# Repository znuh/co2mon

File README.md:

# CO2 multimon

CO2 monitor with support for different sensors, displays and microcontrollers.

Firmware and the printed circuit board include support for all of these components.
No special boards or firmware versions are needed. Sensors and the display are automatically detected by the firmware.

## Supported CO2 sensors
* SCD30
* MH-Z14A, MH-Z19B
* T67xx

## Supported displays
* 1.8" SPI TFT (ST7735 controller)
* 1.3" OLED (**must** have the following pinout: Vdd, GND, SCK, SDA - most 0.96" OLED displays will not work!)
**Note:** Try to get the 1.8" TFT instead of the OLED. OLED displays will 'burn out' after approx. 1 month of continous use. Therefor OLED support is meant as a makeshift if you cannot get the TFT.

## Supported microcontrollers

### ATMega328P 'Nano V3' Boards
For this variant you need to solder a few 0805 resistors and 3x SOT-23 components to side B of the PCB.

### STM32F042K6T6 
Fot this variant you need to solder the LQFP-32 controller, a SOT-23 component, the micro-USB connector, a 1210 fuse and a few 0603 passives to side A of the PCB.

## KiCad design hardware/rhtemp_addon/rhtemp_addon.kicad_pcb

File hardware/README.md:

## further ideas
* add Vdd/GND labels to OLED connector
* use other micro-USB connector? (current choice is hard to solder by hand)
* 3D printed case? (might need larger PCB?)
* add-on board for temp./humidity

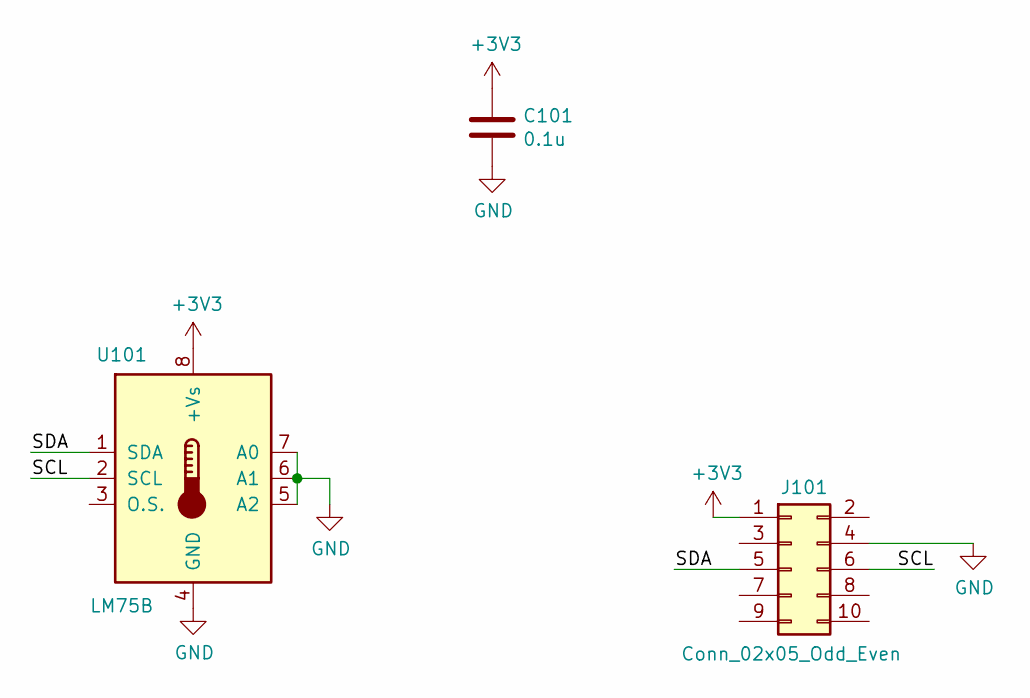
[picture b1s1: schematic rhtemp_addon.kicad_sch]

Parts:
C101: 0.1u; C_0603_1608Metric
J101: Conn_02x05_Odd_Even; PinSocket_2x05_P2.54mm_Vertical
U101: LM75B; SOIC-8_3.9x4.9mm_P1.27mm

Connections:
+3V3: C101.1, J101.1, U101.8 (+Vs)
/SCL: J101.6, U101.2 (SCL)
/SDA: J101.5, U101.1 (SDA)
GND: C101.2, J101.4, U101.4 (GND), U101.5 (A2), U101.6 (A1), U101.7 (A0)

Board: 2 copper layers, 3 parts (1 on the bottom side), 4 nets, no tracks yet.

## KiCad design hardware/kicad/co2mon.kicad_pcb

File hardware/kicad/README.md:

## important: kicad-nightly needed!

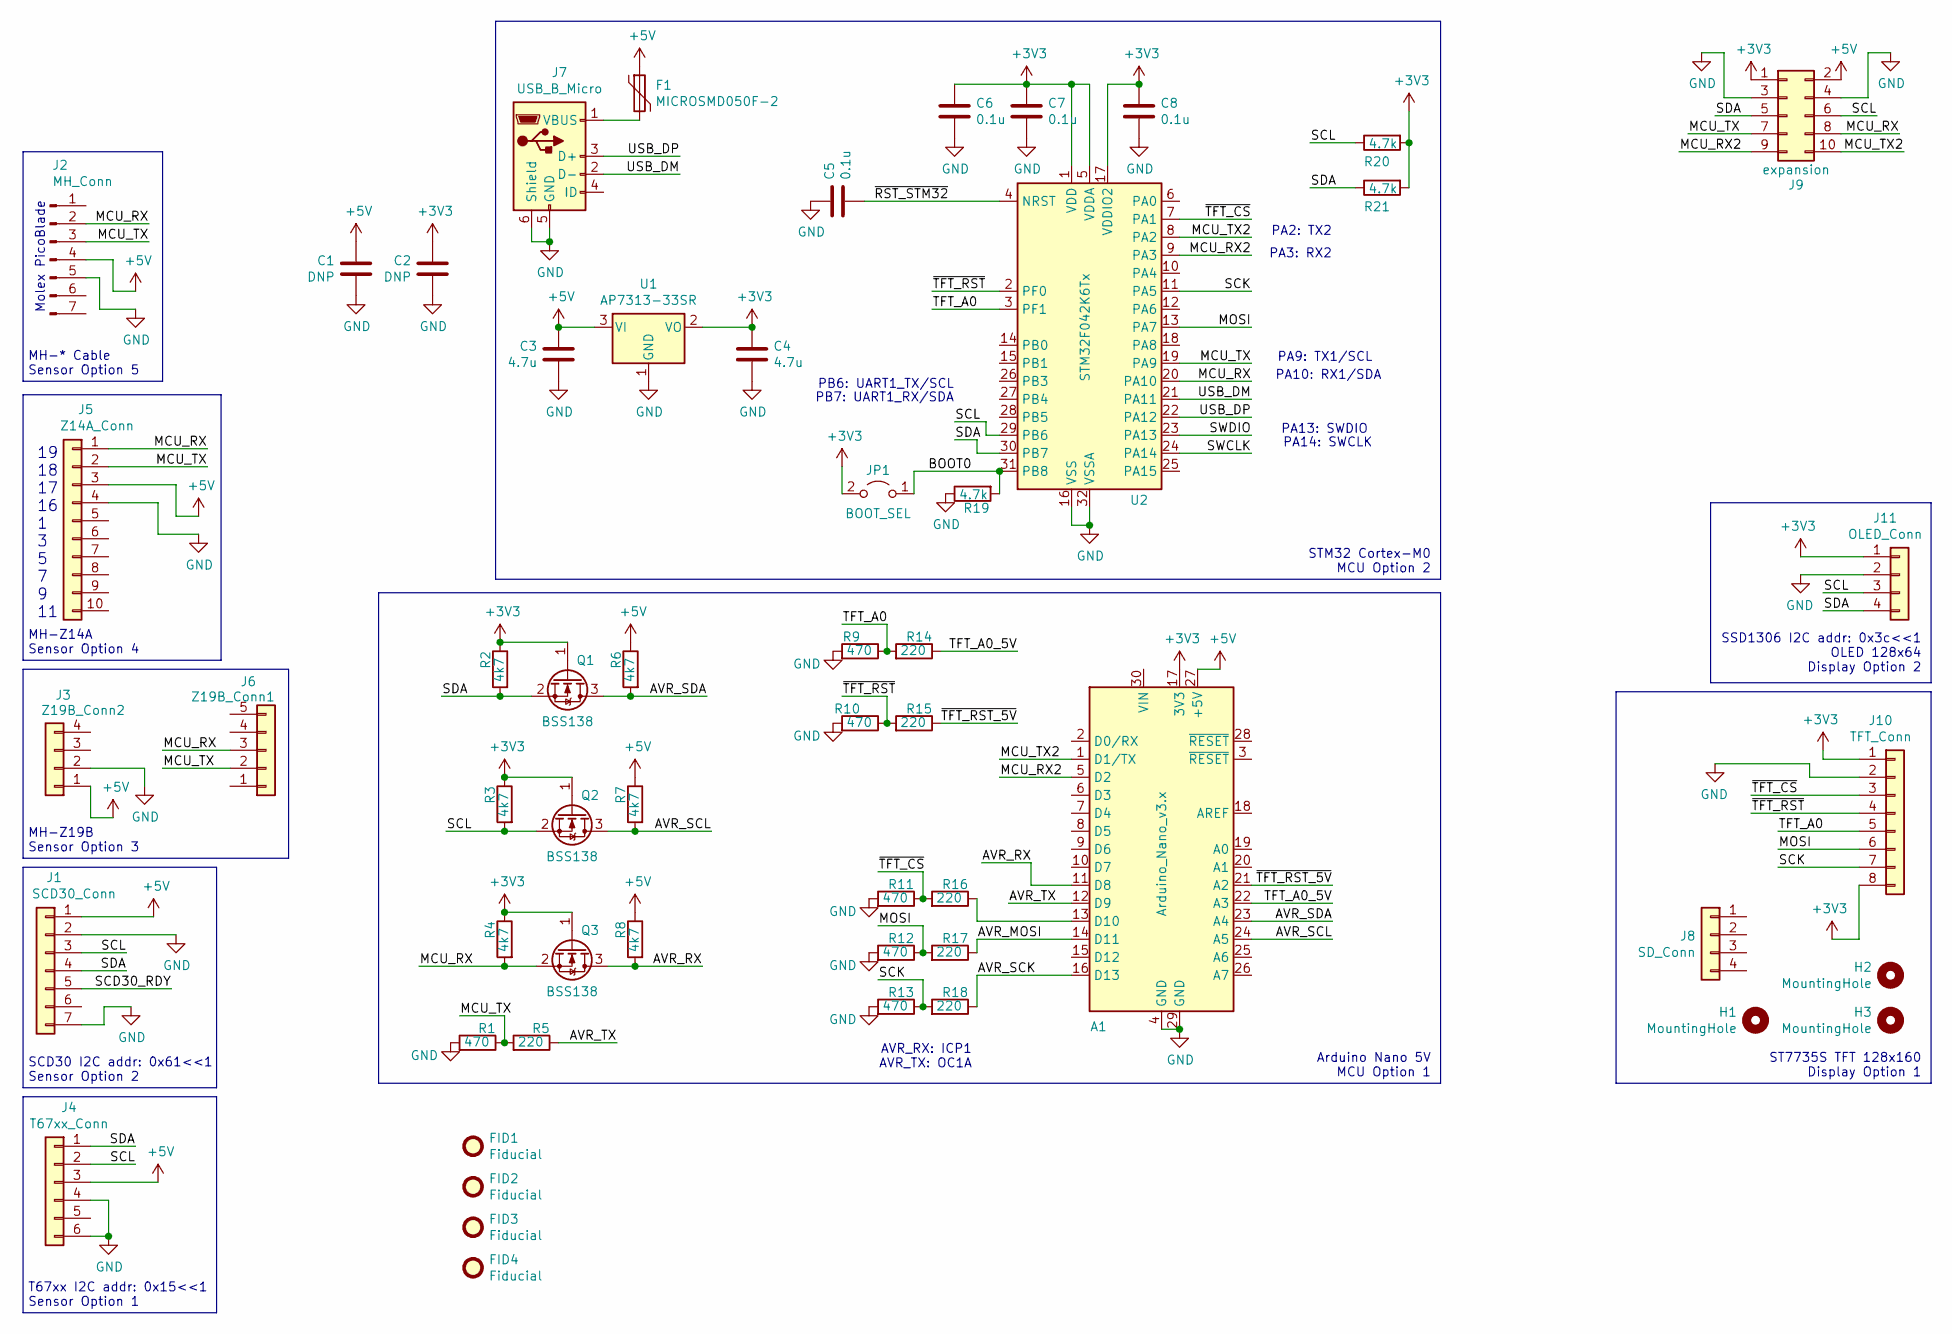
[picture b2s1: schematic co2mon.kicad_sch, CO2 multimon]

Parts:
A1: Arduino_Nano_v3.x; Arduino_Nano
C1, C2: DNP; C_0805_2012Metric_Pad1.15x1.40mm_HandSolder
C3, C4: 4.7u; C_0603_1608Metric
C5, C6, C7, C8: 0.1u; C_0603_1608Metric
F1: MICROSMD050F-2; Fuse_1210_3225Metric
FID1, FID2, FID3, FID4: Fiducial; Fiducial_0.5mm_Mask1.5mm
H1, H2, H3: MountingHole; MountingHole_3.2mm_M3
J1: SCD30_Conn; PinSocket_1x07_P2.54mm_Vertical
J2: MH_Conn; Molex_PicoBlade_53048-0710_1x07_P1.25mm_Horizontal
J3: Z19B_Conn2; PinSocket_1x04_P2.54mm_Vertical
J4: T67xx_Conn; PinSocket_1x06_P2.54mm_Vertical
J5: Z14A_Conn; PinSocket_1x10_P2.54mm_Vertical
J6: Z19B_Conn1; PinSocket_1x05_P2.54mm_Vertical
J7: USB_B_Micro; USB_Micro-B_Molex-105017-0001
J8: SD_Conn; PinSocket_1x04_P2.54mm_Vertical
J9: expansion; PinHeader_2x05_P2.54mm_Vertical
J10: TFT_Conn; PinSocket_1x08_P2.54mm_Vertical
J11: OLED_Conn; PinSocket_1x04_P2.54mm_Vertical
JP1: BOOT_SEL; PinHeader_1x02_P2.54mm_Vertical
Q1, Q2, Q3: BSS138; SOT-23
R1, R9, R10, R11, R12, R13: 470; R_0805_2012Metric_Pad1.15x1.40mm_HandSolder
R2, R3, R4, R6, R7, R8: 4k7; R_0805_2012Metric_Pad1.15x1.40mm_HandSolder
R5, R14, R15, R16, R17, R18: 220; R_0805_2012Metric_Pad1.15x1.40mm_HandSolder
R19, R20, R21: 4.7k; R_0603_1608Metric
U1: AP7313-33SR; SOT-23
U2: STM32F042K6Tx; LQFP-32_7x7mm_P0.8mm

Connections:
+3V3: A1.17 (3V3), C2.2, C4.2, C6.2, C7.2, C8.2, J9.1, J10.1, J10.8, J11.1, JP1.2 (B), Q1.1 (G), Q2.1 (G), Q3.1 (G), R2.1, R3.1, R4.1, R20.2, R21.2, U1.2 (VO), U2.1 (VDD), U2.5 (VDDA), U2.17 (VDDIO2)
+5V: A1.27 (+5V), C1.2, C3.2, F1.1, J1.1, J2.4, J3.1, J4.3, J5.3, J9.2, R6.1, R7.1, R8.1, U1.3 (VI)
/AVR_MOSI: A1.14 (D11), R17.1
/AVR_RX: A1.11 (D8), Q3.3 (D), R8.2
/AVR_SCK: A1.16 (D13), R18.1
/AVR_SCL: A1.24 (A5), Q2.3 (D), R7.2
/AVR_SDA: A1.23 (A4), Q1.3 (D), R6.2
/AVR_TX: A1.12 (D9), R5.1
/BOOT0: JP1.1 (A), R19.2, U2.31 (PB8)
/MCU_RX: J2.2, J5.1, J6.3, J9.8, Q3.2 (S), R4.2, U2.20 (PA10)
/MCU_RX2: A1.5 (D2), J9.9, U2.9 (PA3)
/MCU_TX: J2.3, J5.2, J6.2, J9.7, R1.1, R5.2, U2.19 (PA9)
/MCU_TX2: A1.1 (D1/TX), J9.10, U2.8 (PA2)
/MOSI: J10.6, R12.1, R17.2, U2.13 (PA7)
/SCD30_RDY: J1.5
/SCK: J10.7, R13.1, R18.2, U2.11 (PA5)
/SCL: J1.3, J4.2, J9.6, J11.3, Q2.2 (S), R3.2, R20.1, U2.29 (PB6)
/SDA: J1.4, J4.1, J9.5, J11.4, Q1.2 (S), R2.2, R21.1, U2.30 (PB7)
/SWCLK: U2.24 (PA14)
/SWDIO: U2.23 (PA13)
/TFT_A0: J10.5, R9.1, R14.2, U2.3 (PF1)
/TFT_A0_5V: A1.22 (A3), R14.1
/USB_DM: J7.2 (D-), U2.21 (PA11)
/USB_DP: J7.3 (D+), U2.22 (PA12)
/~RST_STM32: C5.1, U2.4 (NRST)
/~TFT_CS: J10.3, R11.1, R16.2, U2.7 (PA1)
/~TFT_RST: J10.4, R10.1, R15.2, U2.2 (PF0)
/~TFT_RST_5V: A1.21 (A2), R15.1
GND: A1.4 (GND), A1.29 (GND), C1.1, C2.1, C3.1, C4.1, C5.2, C6.1, C7.1, C8.1, J1.2, J1.7, J2.5, J3.2, J4.4, J4.6, J5.4, J7.5 (GND), J7.6 (Shield), J9.3, J9.4, J10.2, J11.2, R1.2, R9.2, R10.2, R11.2, R12.2, R13.2, R19.1, U1.1 (GND), U2.16 (VSS), U2.32 (VSSA)
unnamed: A1.13 (D10), R16.1
unnamed: F1.2, J7.1 (VBUS)

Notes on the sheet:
MH-* Cable Sensor Option 5
MH-Z14A Sensor Option 4
MH-Z19B Sensor Option 3
SCD30 I2C addr: 0x61<<1 Sensor Option 2
T67xx I2C addr: 0x15<<1 Sensor Option 1
19 18 17 16 1 3 5 7 9 11
Molex PicoBlade
PB6: UART1_TX/SCL
PB7: UART1_RX/SDA
AVR_RX: ICP1 AVR_TX: OC1A
PA2: TX2
PA3: RX2
PA13: SWDIO
PA9: TX1/SCL
PA14: SWCLK
PA10: RX1/SDA
STM32 Cortex-M0 MCU Option 2
Arduino Nano 5V MCU Option 1
SSD1306 I2C addr: 0x3c<<1 OLED 128x64 Display Option 2
ST7735S TFT 128x160 Display Option 1

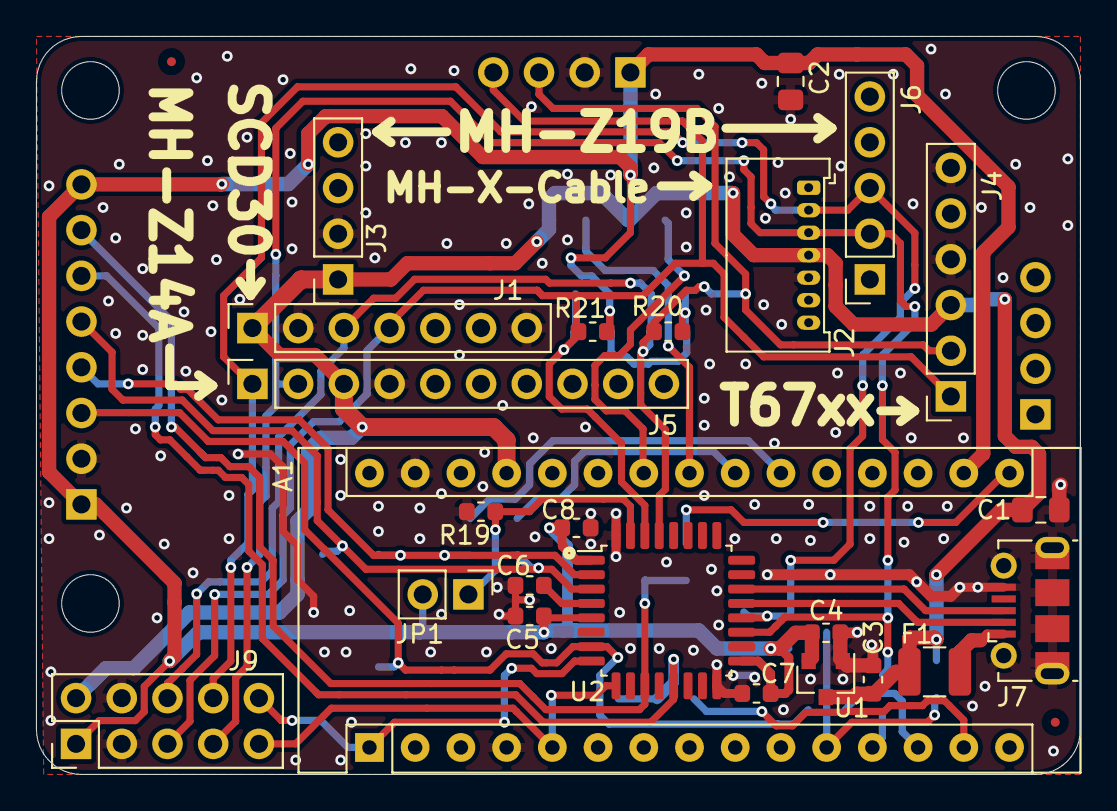
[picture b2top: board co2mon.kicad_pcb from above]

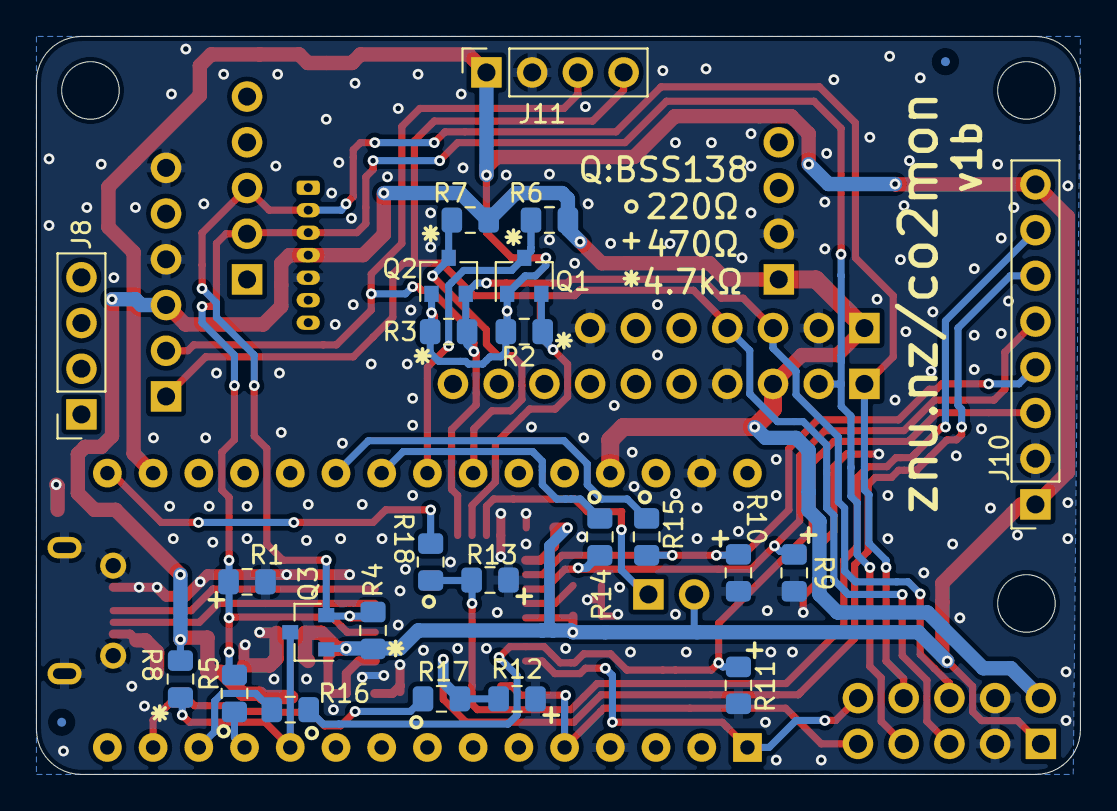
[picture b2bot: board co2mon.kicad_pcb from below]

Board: 2 copper layers, 58.0 x 41.0 mm, 55 parts (26 on the bottom side), 28 nets.

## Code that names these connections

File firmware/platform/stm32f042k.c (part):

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
/* IO assignments:
 * 
 * PA1 :             ~TFT_CS
 * PA2 : TX2     AF1 MCU_TX2   - RFU
 * PA3 : RX2     AF1 MCU_RX2   - RFU
 * PA5 : SCK     AF0 TFT_CLK
 * PA7 : MOSI    AF0 TFT_DATA
 * PA9 : TX1     AF1 TXD_S - to sensor
 * PA10: RX1     AF1 RXD_S - from sensor
 * PA11: USB_DM  
 * PA12: USB_DP
 * 
 * PB6 : SCL     AF1
 * PB7 : SDA     AF1
 * 
 * PF0 :             ~TFT_RST
 * PF1 :             TFT_A0
 */

static const uint32_t gpio_map[3][2] = {
	{GPIOA, GPIO1},  /* GPIO_TFT_NCS   */
	{GPIOF, GPIO0},  /* GPIO_TFT_NRST  */
	{GPIOF, GPIO1}   /* GPIO_TFT_A0 */
};

static inline void spi_busywait(uint32_t spi) {
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
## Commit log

2020-11-03 initial import
2020-11-03 rename makefile
2020-11-03 add libopencm3 submodule
2020-11-03 working on stm32, fix some compiler warnings
2020-11-03 more compiler warning fixes
2020-11-03 add non-stm32 targets to new common Makefile
2020-11-03 use one Makefile for all targets
2020-11-03 add firmware size info for stm32
2020-11-03 rename gpio_set to avoid namespace collisions w/ libopencm3, start working on stm32 code
2020-11-03 add stm32 IO assignments
2020-11-03 stm32: WIP
2020-11-03 respect jiffies uint32 rollover case
2020-11-03 stm32++
2020-11-03 stm32 UART
2020-11-03 use time constant
2020-11-03 note
2020-11-03 msleep(10) in AVR hw_init no longer needed w/ msleep(100) after hw_init in main
2020-11-03 more i2c init stuff
2020-11-03 working on stm32 i2c
2020-11-03 dfu-util command for stm32 firmware upload
2020-11-03 msleep must wait at least 1 increment longer b/c current timer cycle has already started
2020-11-03 fixes for stm32 gpio init
2020-11-03 fixes for SPI and UART - SPI+UART working on STM32
2020-11-04 typo
2020-11-04 working on stm32 i2c code
2020-11-04 stm32 i2c wip
2020-11-04 stm32 i2c write
2020-11-04 needs some debugging...
2020-11-05 switch to software i2c implementation - due to i2c peripheral errata listed in ES0243 rev 3
2020-11-05 software i2c WIP
2020-11-05 testing time...
2020-11-05 partially working, still a bit buggy
2020-11-05 move crc8 to utils
2020-11-05 fix for stupid bug in stm32 software i2c
2020-11-05 pointer sanity check not needed
2020-11-05 do proper crc checks for SHTC3 sensor
2020-11-05 use two quarter-cycles instead of two half-cycles for SCL low
2020-11-05 i2c timings tuned a bit
2020-11-05 fix for shtc3 crc off-by-one error
2020-11-05 stm32 works
2020-11-05 clarify flash mem / read definitions
2020-11-05 working on better timeout approach
2020-11-05 add comment w/ font datasize
2020-11-06 whitespace--
2020-11-06 better OLED digits added
2020-11-06 don't require libopencm3 for AVR build
2020-11-06 one more TODO
2020-11-06 new timeout code w/ timer rollover handling
2020-11-06 fix for timeout code
2020-11-06 move SHTC3 to top of sensors list
2020-11-06 i2c timeout fix for atmega328p
2020-11-06 reorder sensors list
2020-11-08 always print 'ppm CO2' string on OLED, use stdout on linux
2020-11-08 bump firmware version to rc1
2020-11-08 remove remnants of stm32 i2c peripheral
2020-11-08 revert previous "fix" for OLED display - doesn't fix the actual problem
2020-11-08 add note about kicad-nightly
2020-11-08 remove temp/humidity sensor
2020-11-08 add schematics and gerber files
2020-11-08 basic instructions
2020-11-09 initialize expired value
2020-11-09 argh! reading a uint16_t obviously isn't atomic on AVR arch /o\
2020-11-09 don't use unicode degree sign for serial output
2020-11-09 update firmware instructions
2020-11-09 update BOM exclusions
2020-11-09 add BOMs
2020-11-09 fix typos
2020-11-09 remove outdated notes
2020-11-09 AVR timeout bug fixed - bump version
2020-11-10 hw notes
2020-11-12 working on rh/temp addon board
2020-11-15 working on stm32 usb data output
2020-11-15 stm32 usb wip
2020-11-15 ignore usb writes if no host present
2020-11-15 support switching back to bootloader via USB
2020-11-19 use unicode degree sign
2020-11-19 make stm32 bootloader invocation more robust, add stm32 USB tx, bump version to -rc3
2020-11-23 make flashing stm32 work when already in bootloader
2022-04-23 make USB disconnect for bootloader entry more reliable
2023-06-14 don't pull I2C low on init
2025-02-12 fix: use correct GPIO port for USB disconnect (GPIOA instead of GPIOB)

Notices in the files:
firmware/platform/stm32f042k.c:
Copyright (C) 2020 Benedikt Heinz <hunz@mailbox.org>
This is free software: you can redistribute it and/or modify
it under the terms of the GNU General Public License as published by
the Free Software Foundation, either version 3 of the License, or
(at your option) any later version.
hardware/kicad/co2mon.kicad_sch:
License: CC-BY-SA 4.0
